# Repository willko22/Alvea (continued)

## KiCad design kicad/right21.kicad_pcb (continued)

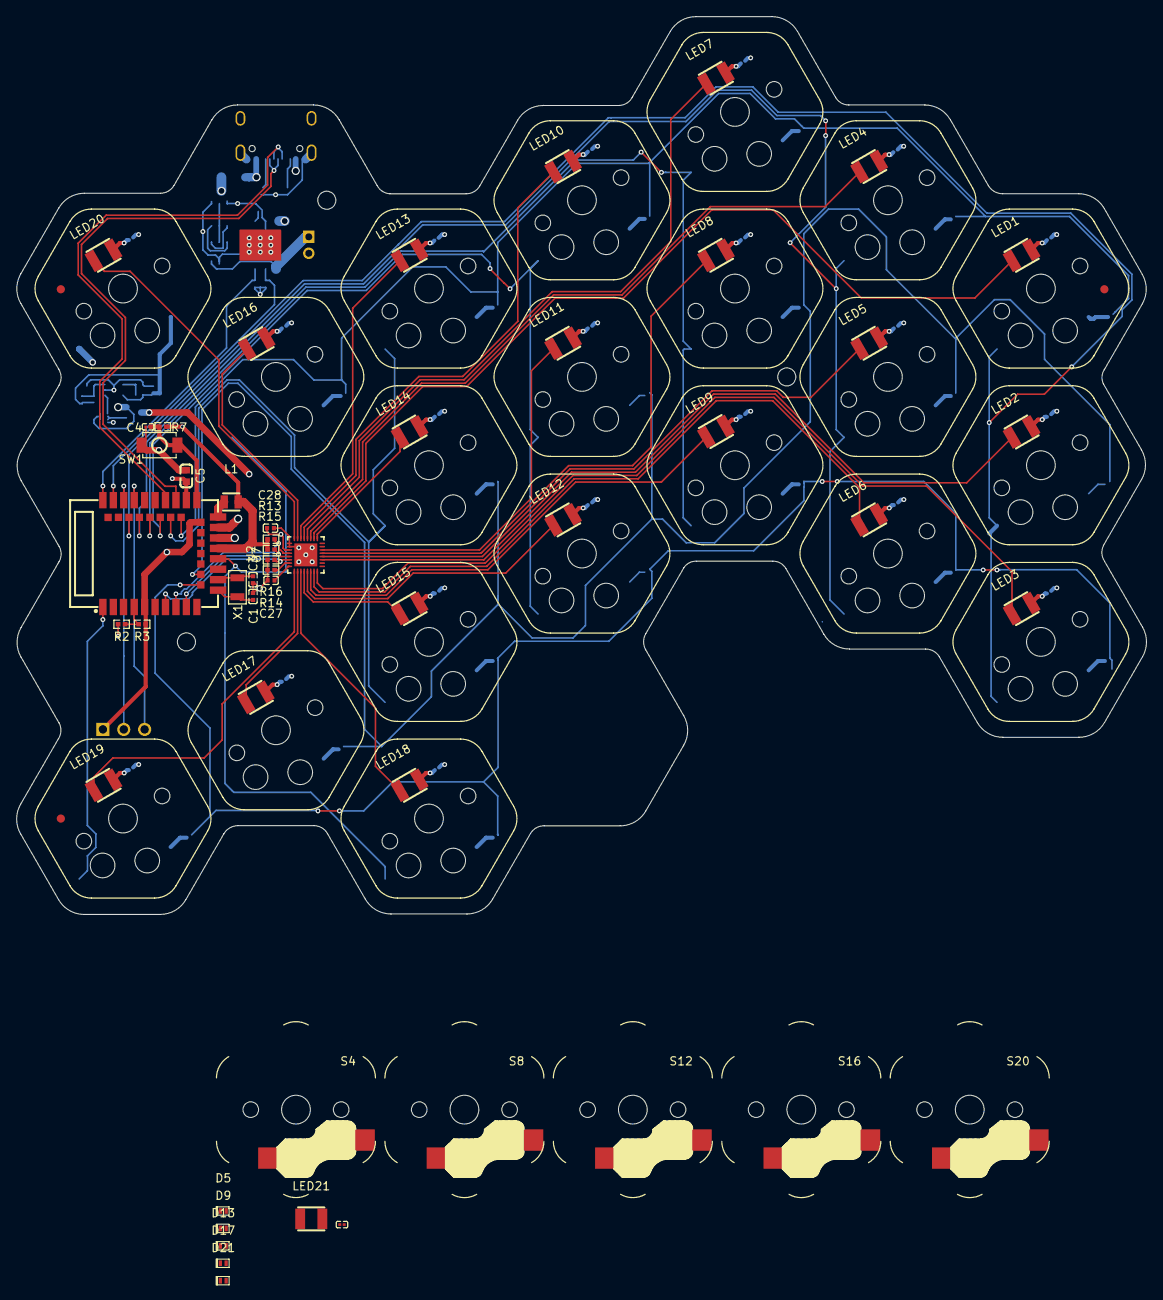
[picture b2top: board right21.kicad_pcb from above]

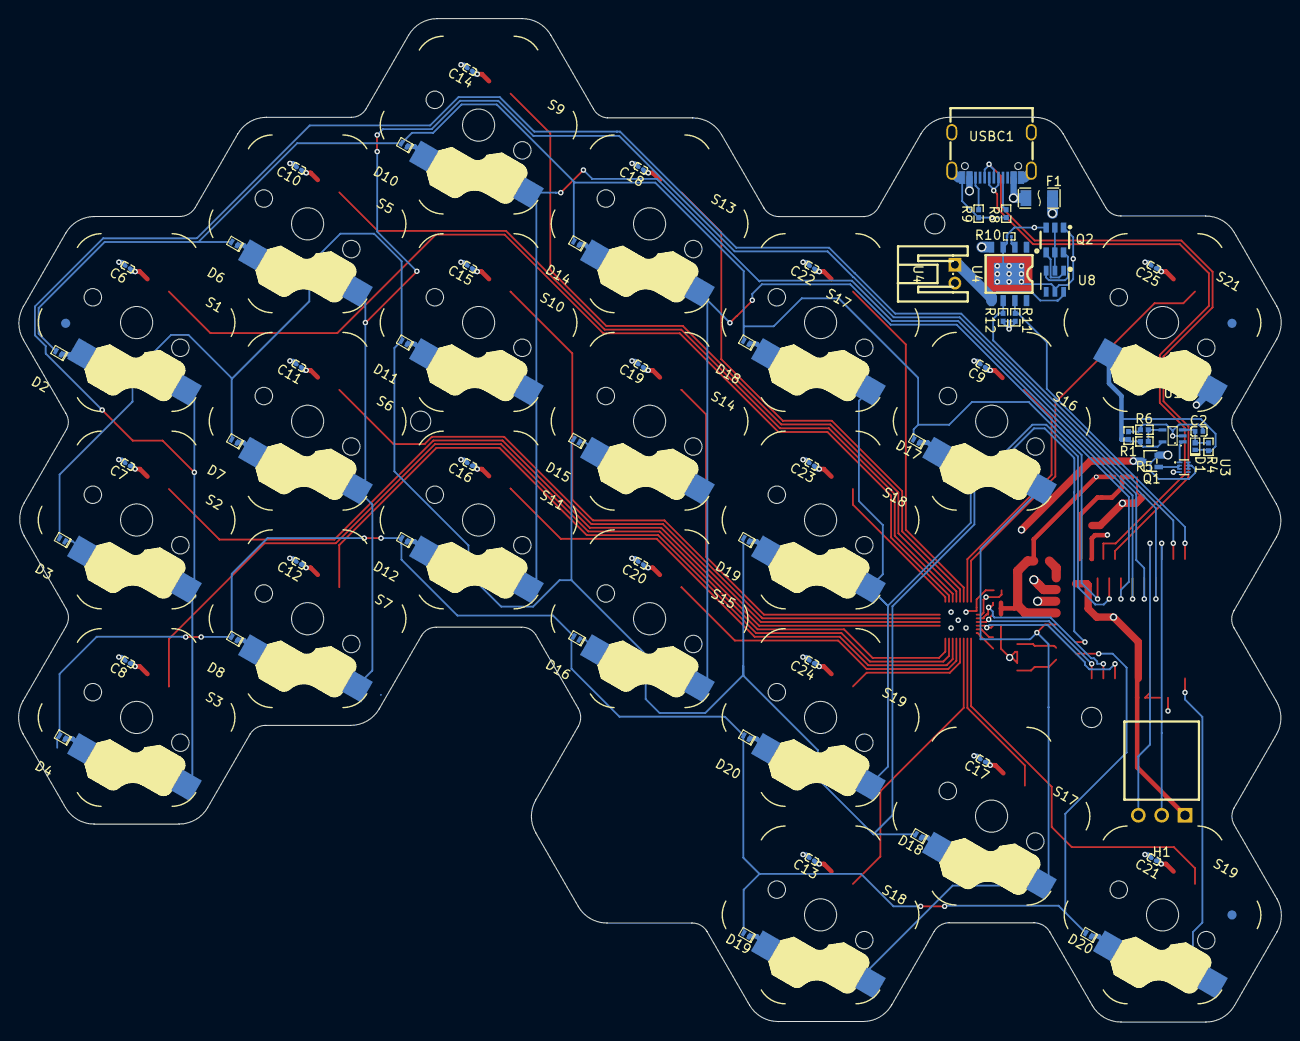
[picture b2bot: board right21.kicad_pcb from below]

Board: 4 copper layers, 137.5 x 109.3 mm, 166 parts (93 on the bottom side), 84 nets.

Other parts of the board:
Battery?: 3500mAh LiPo
D17#2, D18#2, D19#2, D20#2: CDSQC4148-HF; X1-DFN1006-2_L1.0-W0.6-RD
Fi1, Fi2, Fi3, Fi6: Fiducial_1mm_Mask2mm
Fi4, Fi5: Fiducial_1mm_Mask2mm
G**: LOGO; handy
M2: MountingHole_2.2mm_M2
S16#2, S17#2, S18#2, S19#2: Choc HEX; PG1350_hotswap
U4#2: S2B-PH-K-S(LF)(SN); CONN-TH_S2B-PH-K-S-LF-SN
U8: DW01A_C42380662; SOT-23-6_L2.9-W1.6-P0.95-LS2.9-BL
component_case_outline: PG1350_hotswap
component_case_outline#2, component_case_outline#3, component_case_outline#4, component_case_outline#5: PG1350_hotswap
component_safe_space: PG1350_hotswap
component_safe_space#2, component_safe_space#3: PG1350_hotswap
hex_edge: b9cf7df6-7b49-4194-bf11-16aaca528749
hex_edge#2, hex_edge#3, hex_edge#4, hex_edge#5, hex_edge#6, hex_edge#7, hex_edge#8, hex_edge#9, hex_edge#10, hex_edge#11, hex_edge#12, hex_edge#13, hex_edge#14, hex_edge#15, hex_edge#16, hex_edge#17, hex_edge#18: b9cf7df6-7b49-4194-bf11-16aaca528749
key_template: PG1350_hotswap

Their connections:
/BAT+: U4#2.1, U8.6 (VSS); also elsewhere on the board
/COL6: S16#2.1, S17#2.1, S18#2.1
/ROW3: D19#2.2, D20#2.2; also elsewhere on the board
unnamed 62: D17#2.1, S16#2.2; also elsewhere on the board
unnamed 63: D18#2.1, S17#2.2; also elsewhere on the board
unnamed 64: D19#2.1, S18#2.2; also elsewhere on the board
unnamed 65: D20#2.1, S19#2.2; also elsewhere on the board
unnamed 68: U8.3 (CO); also elsewhere on the board
unnamed 69: U8.1 (DO); also elsewhere on the board
unnamed 78: U8.2 (VM); also elsewhere on the board

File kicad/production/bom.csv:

Designator,Footprint,Quantity,Value,LCSC Part #
", HEX_EDGE_18, HEX_EDGE_17, HEX_EDGE_16, HEX_EDGE_15, HEX_EDGE_14, HEX_EDGE_13, HEX_EDGE_12, HEX_EDGE_11, HEX_EDGE_10, HEX_EDGE_9, HEX_EDGE_8, HEX_EDGE_7, HEX_EDGE_6, HEX_EDGE_5, HEX_EDGE_4, HEX_EDGE_3, HEX_EDGE_2",b9cf7df6-7b49-4194-bf11-16aaca528749,18,,
BATTERY?,3500mAh LiPo,1,3500mAh LiPo,
C1,C0402,1,GRM155Z71A105KE01D,C528974
"C10, C11, C12, C13, C14, C15, C16, C17, C18, C19, C20, C21, C22, C23, C24, C25, C4, C6, C7, C8, C9",C0201,21,GRM033C71C104KE14D,C85923
"C2, C3",C0402,2,0402CG120F500NT,C182477
"C26, C27",C0402,2,GRM155C71C105KE11D,C576449
C5,C0603,1,GRM188C71C475KE21D,C237615
D1,DSN2_L1.0-W0.6-RD,1,NSR05F20NXT5G,C94366
"D10, D11, D12, D13, D14, D15, D16, D17, D18, D19, D2, D20, D3, D4, D5, D6, D7, D8, D9",X1-DFN1006-2_L1.0-W0.6-RD,19,CDSQC4148-HF,C6341459
F1,F1206,1,SMD1206-150C-16V,C2760275
L1,IND-SMD_L2.0-W1.6_BRC2016,1,BRC2016T100K,C223154
Q1,SOT-323-3_L2.0-W1.3-P1.30-LS2.1-BR,1,"PMF170XP,115",C389353
Q2,SOT-23-6_L2.9-W1.6-P0.95-LS2.8-BR,1,FS8205A_C2830320,C2830320
R1,R0402,1,RC0402FR-07100KL,C60491
R10,R0201,1,RC0201FR-07680RL,C274876
"R11, R12, R7",R0402,3,RC0402FR-0710KL,C60490
R13,R0402,1,RT0402BRD0737K4L,C852746
"R14, R15, R8, R9",R0402,4,RC0402FR-075K1L,C105872
"R16, R4, R6",R0402,3,RC0402FR-071ML,C138033
"R2, R5",R0402,2,WR04W2494FTL,C368359
R3,R0402,1,RC0402FR-074M3L,C327242
SW1,SW-SMD_L3.9-W3.0-P4.45,1,TS-1088-AR02016,C720477
U1,SC-70-5_L2.0-W1.3-P0.65-LS2.1-BR,1,TLV7031QDCKRQ1,C3658630
U2,WIRELM-SMD_E73-2G4M08S1C,1,E73-2G4M08S1C,C356849
U3,X2SON-8_L1.4-W1.0-P0.35-BL,1,SN74LVC1G74DQER,C2870716
U4,ESOP-8_L4.9-W3.9-P1.27-LS6.0-BL-EP,1,BL8573CS8TR,C2999147
U5,SOT-23-6,1,DW01A,
U6,CONN-TH_S2B-PH-K-S-LF-SN,1,S2B-PH-K-S(LF)(SN),C173752
U7,VQFN-32_L4.0-W4.0-P0.40-TL-EP,1,LP5024RSMR,C427525
USBC1,USB-C_SMD-TYPE-C-31-M-12_1,1,TYPE-C-31-M-12,C165948
X1,OSC-SMD_L3.2-W1.5,1,FC-13532.768KHZ9PF20PPM,C99010

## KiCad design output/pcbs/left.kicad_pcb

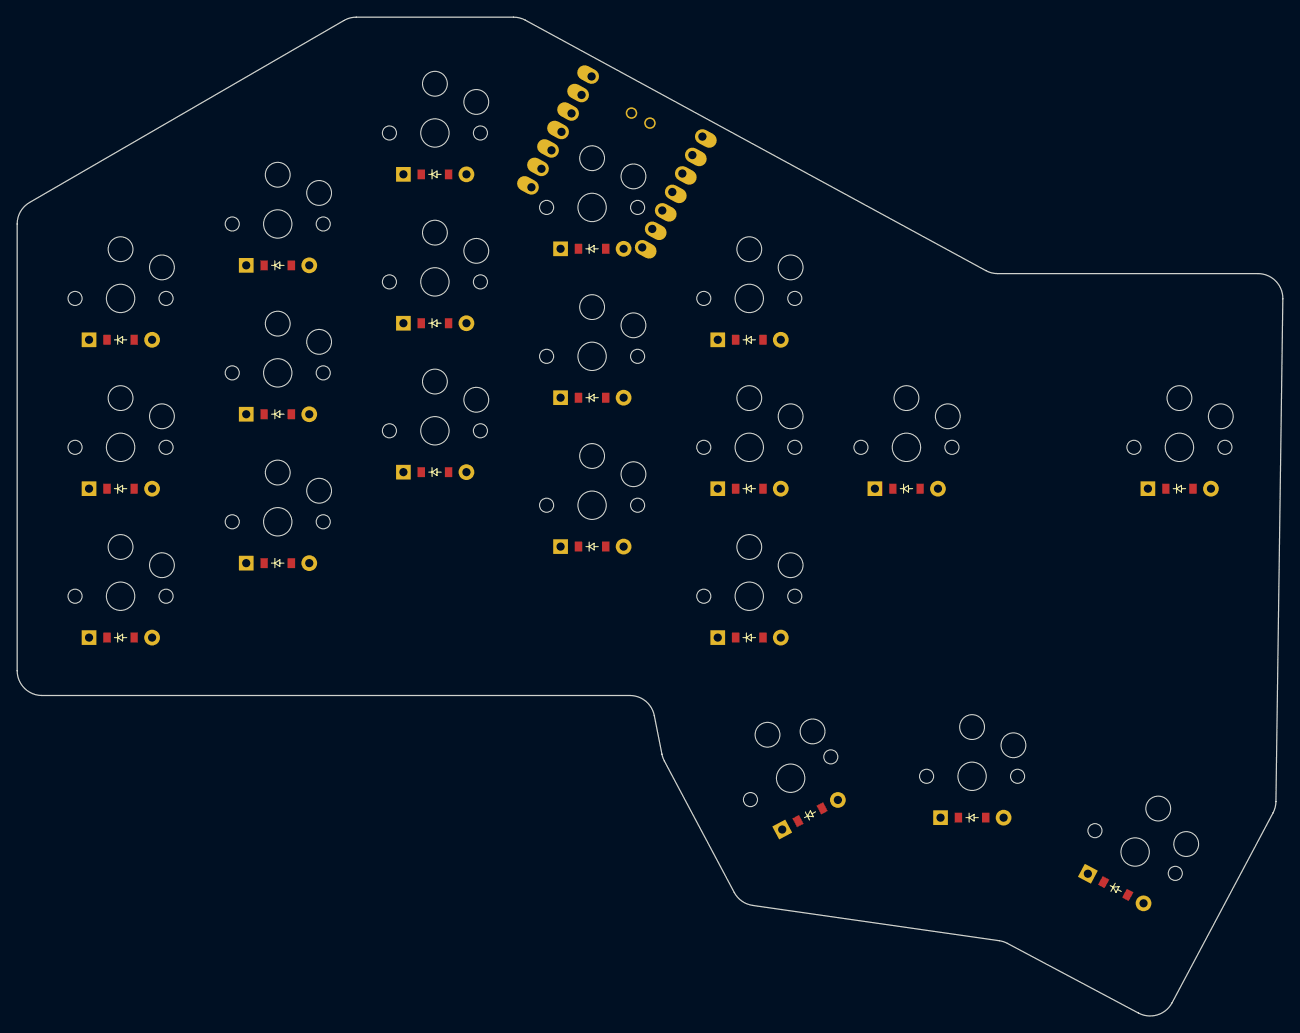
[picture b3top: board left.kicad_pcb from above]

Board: 2 copper layers, 153.0 x 120.7 mm, 41 parts (0 on the bottom side), 21 nets, no tracks yet.

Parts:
D1, D2, D3, D4, D5, D6, D7, D8, D9, D10, D11, D12, D13, D14, D15, D16, D17, D18, D19, D20: ComboDiode
MCU1: XIAO-BLE
S1, S2, S3, S4, S5, S6, S7, S8, S9, S10, S11, S12, S13, S14, S15, S16, S17, S18, S19, S20: PG1350

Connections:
GND: MCU1.13, MCU1.17
index_bottom: D10.2, S10.2
index_home: D11.2, S11.2
index_top: D12.2, S12.2
inner_bottom: D13.2, S13.2
inner_cluster: D16.2, S16.2
inner_home: D14.2, S14.2
inner_top: D15.2, S15.2
middle_bottom: D7.2, S7.2
middle_cluster: D17.2, S17.2
middle_home: D8.2, S8.2
middle_top: D9.2, S9.2
other_cluster: D19.2, S19.2
outer_cluster: D18.2, S18.2
pinky_bottom: D1.2, S1.2
pinky_home: D2.2, S2.2
pinky_top: D3.2, S3.2
power_cluster: D20.2, S20.2
ring_bottom: D4.2, S4.2
ring_home: D5.2, S5.2
ring_top: D6.2, S6.2

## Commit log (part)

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2026-03-06 git init
2026-03-08 a lot... almost done schematic... need to rewire to new mcu module... pcb key/led/diode placement done... other componenets tbd
2026-03-09 changed raw mcu to e73module with antena... cleaned pcb a little
2026-03-10 kicad-backups folder removed
2026-03-10 psb outline
2026-03-12 ... started doing wiring
2026-03-13 finished part placement and wiring. TODO: wire swd pins. mirror the board for left side.
2026-03-16 added art... and some other stuff
2026-03-16 added fiducials
2026-03-17 added mounting holes
2026-03-17 changed mounting holes. cleared a little bit, created 21 key version... needs 21 key integration
2026-03-17 removed 21.... instead ill just move the high index to bottom index
2026-03-18 integrated the move from distant index to lowest index... changed from 7colX3row to 5colX4row
2026-03-18 finished right, i hope
2026-03-19 started left
2026-03-19 moved one mounting hole
2026-04-10 left wiring done... right changed to shmitt inctead of comparator... need to do same on left... fixing of right in progress
2026-04-12 pcb done. schematick done. need to double check schematick and ask in discord about pcb... but else done
2026-04-12 text position changes
2026-04-12 checked and update schematics on off need to update it in pcb...
2026-04-13 started redesign... removed led caps and moved everything to fron layer... need to move debug connector to front and than try to change pcb stack.
2026-05-02 fucking history
2026-05-02 finished. needes inspection. added battery measurer. wired left side
2026-05-03 changed on/off timing resistor to 2M61 0805
2026-05-04 added gnd vias all over the board. went trough schematic again. changed resistor for rc to bigger one in footprint, and smaller one in Ohm. both left and right sides are ready. just need to go over t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
2026-05-11 update vias under led controller... on left part. checking correctness of footprints in progress
2026-05-11 change vias under led controller on right side
2026-05-11 checked most component footprints
2026-05-11 checked and updated all major components
2026-06-21 both sides done. changed few components for their basic or more affordable alternaatives.
2026-06-27 first panelization... changing parts because of availability
2026-06-29 ... todo: update panel woth newest left and right pcb
2026-06-29 added lcsc part # for USBLC6-2SC6
2026-06-29 added readme, design, licenses
